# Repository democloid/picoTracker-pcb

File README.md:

# PCB for PicoTrackerPortable
All data in order to fabricate the PCB for the portable version of [picoTracker](https://github.com/democloid/picoTracker)

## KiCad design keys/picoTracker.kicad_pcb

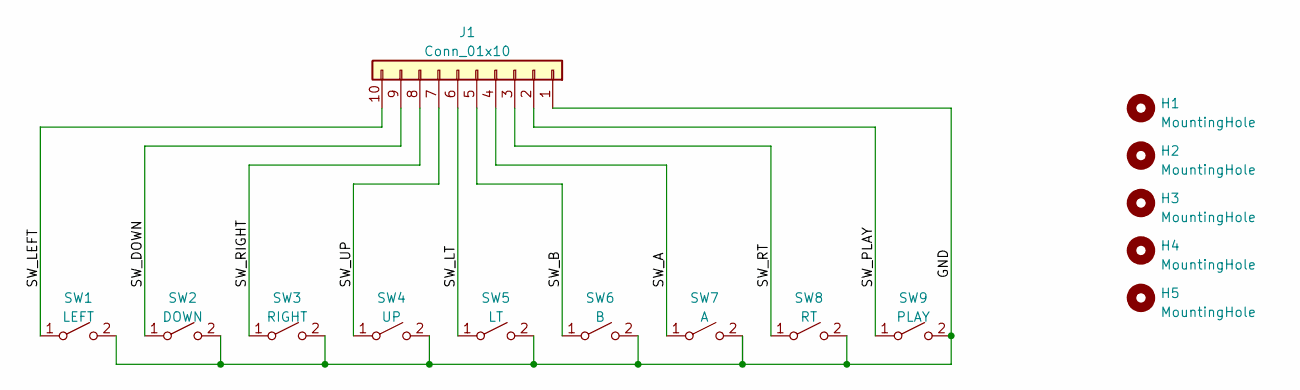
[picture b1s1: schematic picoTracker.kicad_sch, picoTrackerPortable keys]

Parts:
H1, H2, H3, H4, H5: MountingHole; MountingHole_2.2mm_M2
J1: Conn_01x10; PinHeader_1x10_P2.54mm_Vertical
SW1: LEFT; Cherry-MX-Low-Profile
SW2: DOWN; Cherry-MX-Low-Profile
SW3: RIGHT; Cherry-MX-Low-Profile
SW4: UP; Cherry-MX-Low-Profile
SW5: LT; Cherry-MX-Low-Profile
SW6: B; Cherry-MX-Low-Profile
SW7: A; Cherry-MX-Low-Profile
SW8: RT; Cherry-MX-Low-Profile
SW9: PLAY; Cherry-MX-Low-Profile

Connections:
/GND: J1.1, SW1.2 (B), SW2.2 (B), SW3.2 (B), SW4.2 (B), SW5.2 (B), SW6.2 (B), SW7.2 (B), SW8.2 (B), SW9.2 (B)
/SW_A: J1.4, SW7.1 (A)
/SW_B: J1.5, SW6.1 (A)
/SW_DOWN: J1.9, SW2.1 (A)
/SW_LEFT: J1.10, SW1.1 (A)
/SW_LT: J1.6, SW5.1 (A)
/SW_PLAY: J1.2, SW9.1 (A)
/SW_RIGHT: J1.8, SW3.1 (A)
/SW_RT: J1.3, SW8.1 (A)
/SW_UP: J1.7, SW4.1 (A)

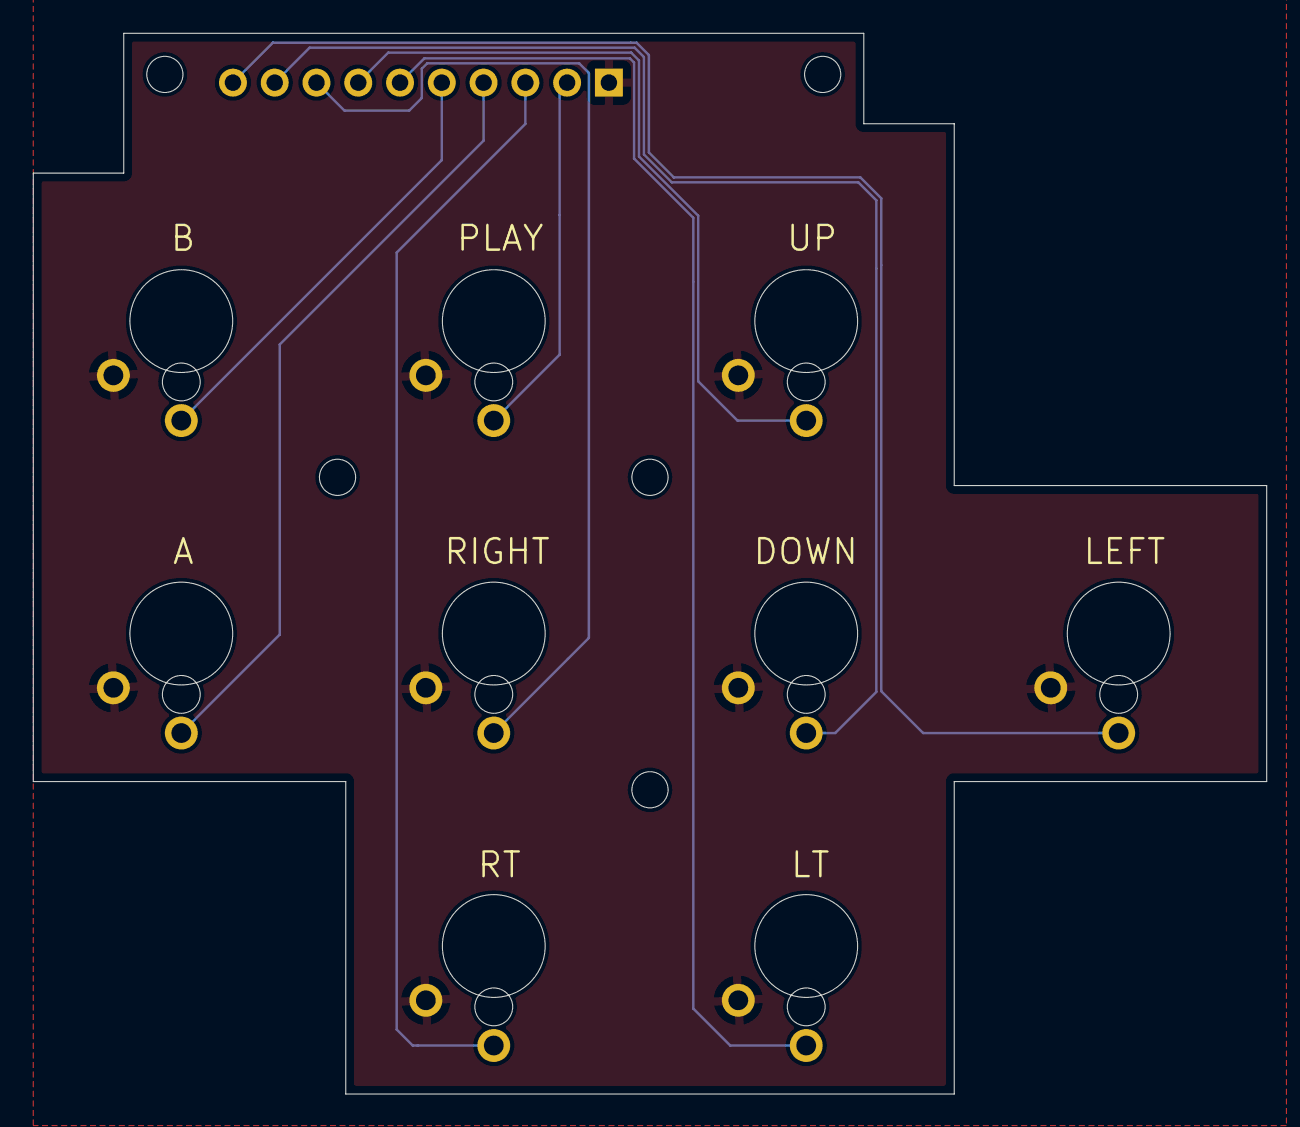
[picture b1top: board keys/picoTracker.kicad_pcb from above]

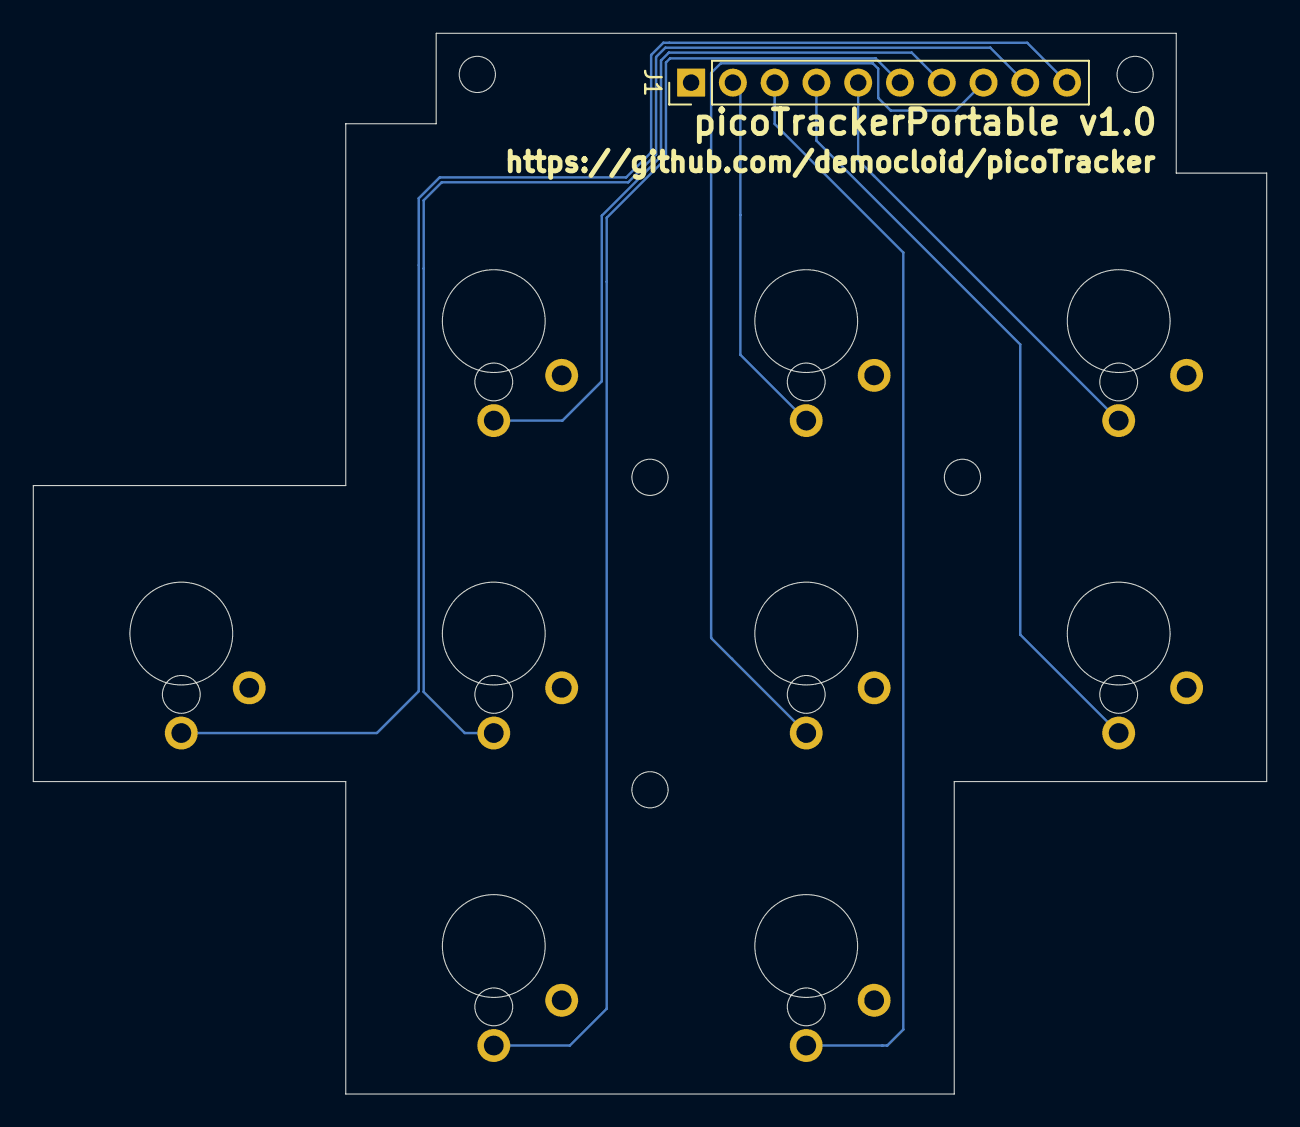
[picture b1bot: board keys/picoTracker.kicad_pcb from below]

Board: 2 copper layers, 75.0 x 64.5 mm, 15 parts (10 on the bottom side), 10 nets.

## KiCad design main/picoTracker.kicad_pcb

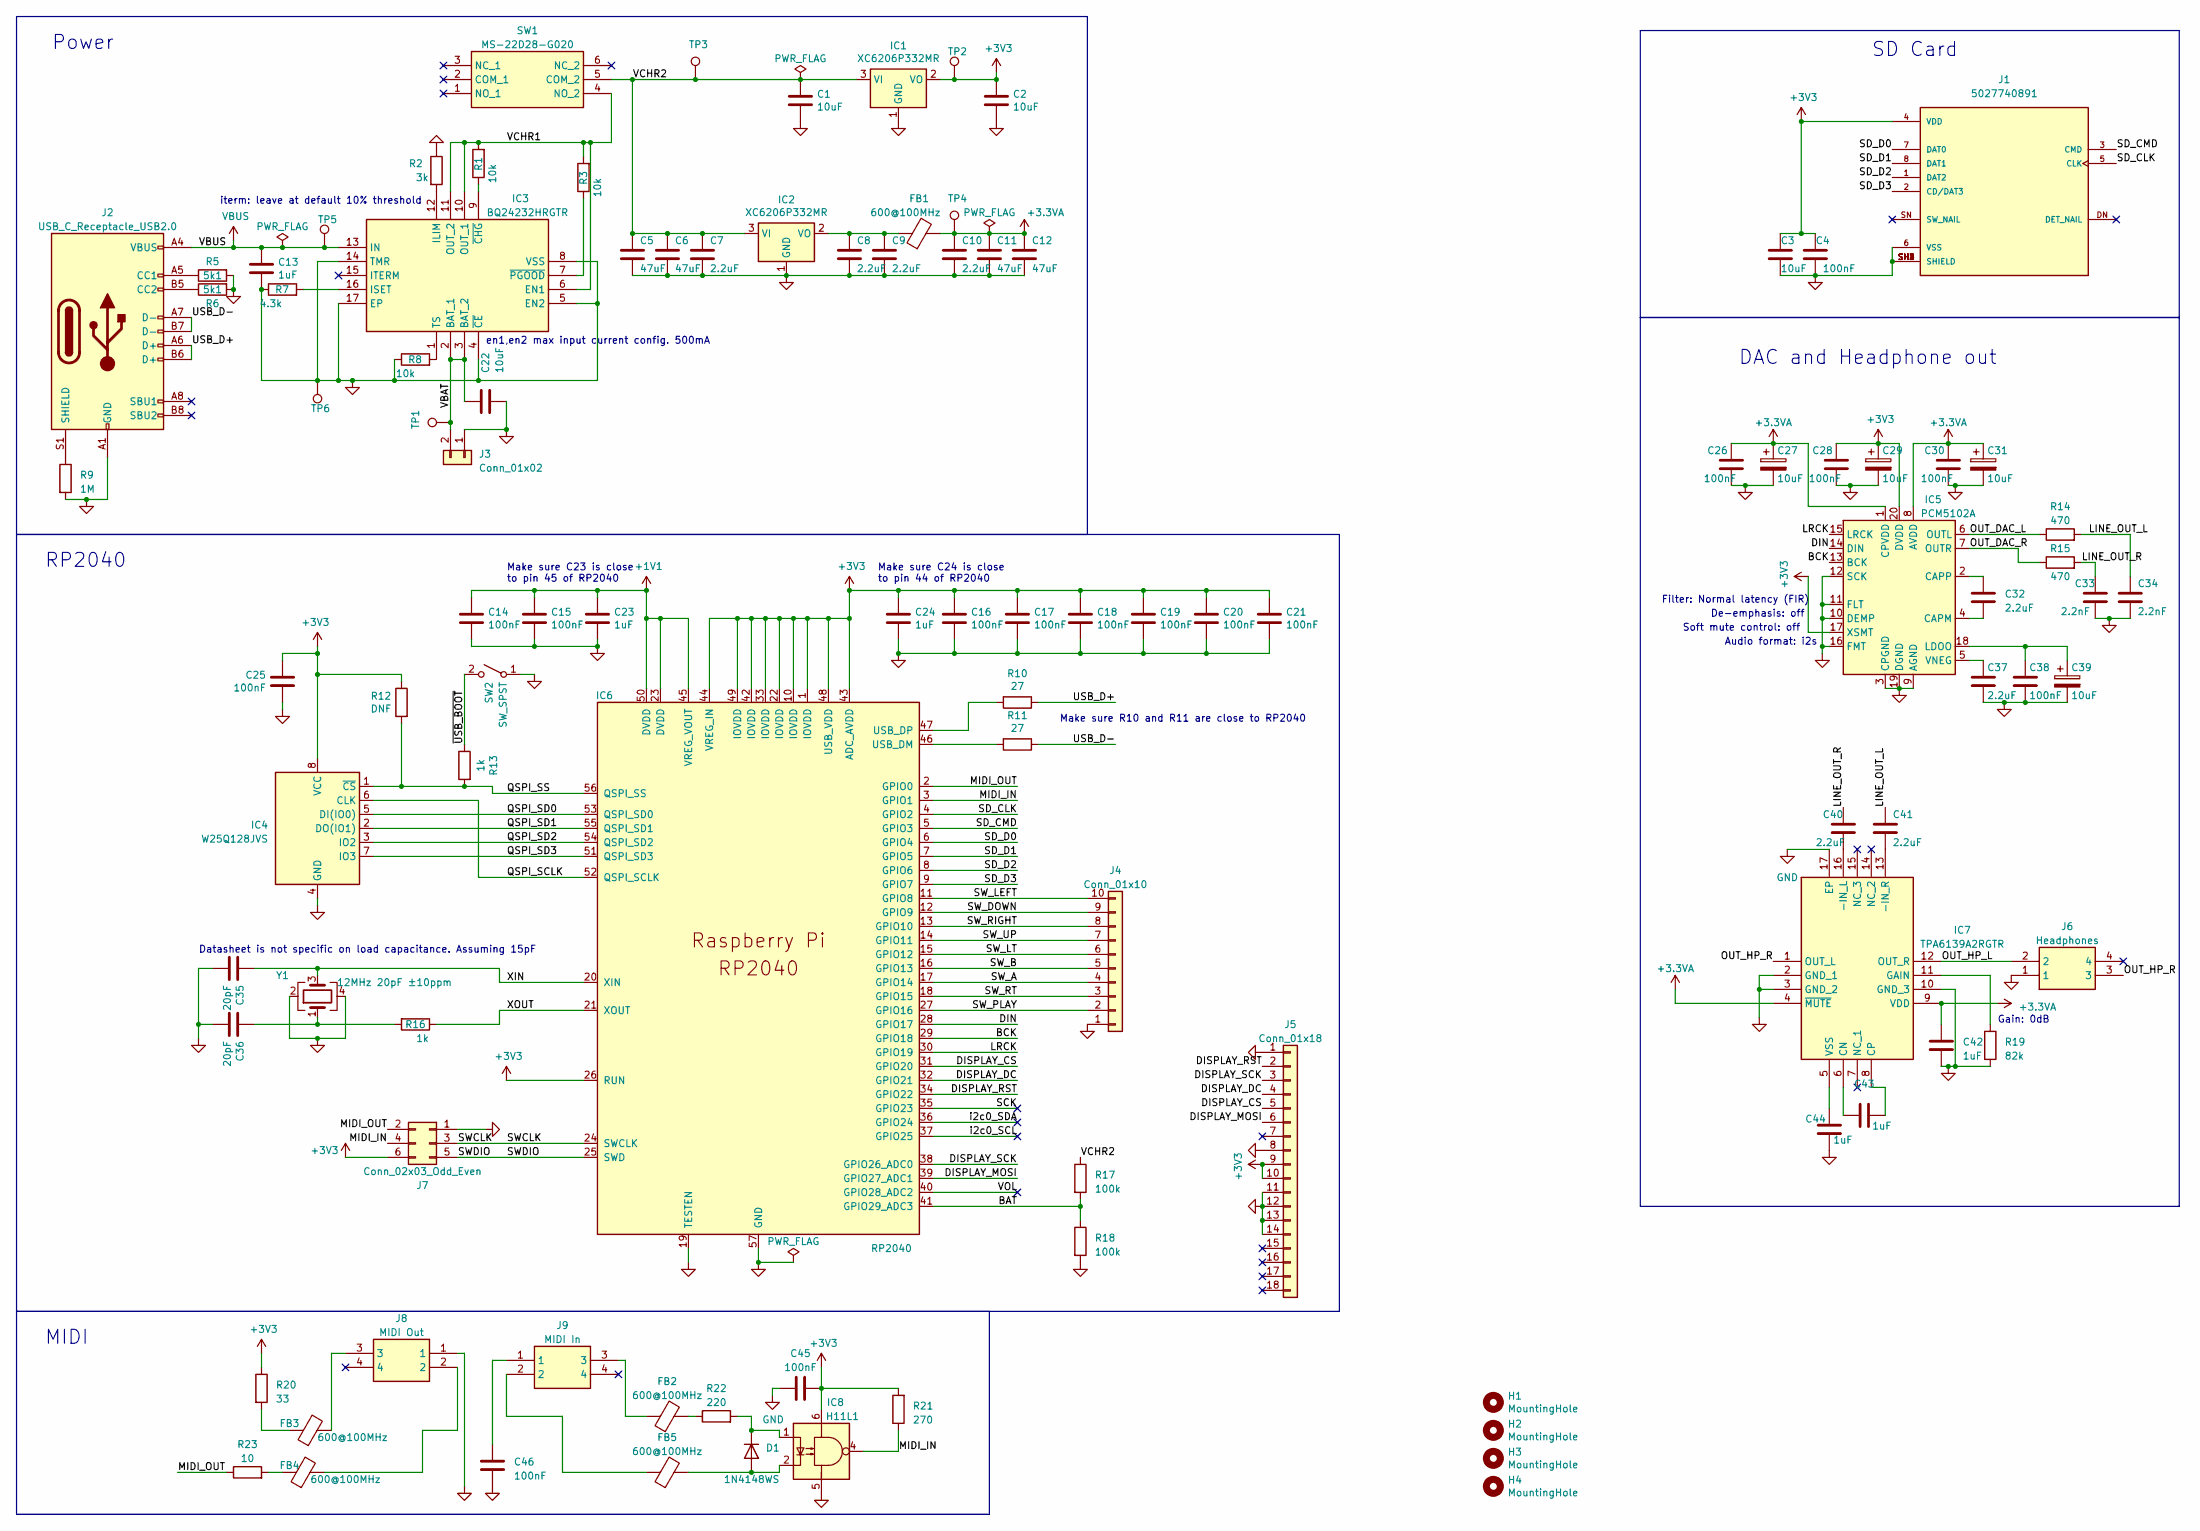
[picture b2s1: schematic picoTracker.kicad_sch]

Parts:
C1, C2, C3, C22: 10uF; C_0603_1608Metric; LCSC C19702
C4, C14, C15, C16, C17, C18, C19, C20, C21, C25, C26, C28, C30, C38, C45, C46: 100nF; C_0603_1608Metric; LCSC C14663
C5, C6, C11, C12: 47uF; C_0805_2012Metric; LCSC C16780
C7, C8, C9, C10, C32, C37, C40, C41: 2.2uF; C_0603_1608Metric; LCSC C23630
C13, C23, C24, C42, C43, C44: 1uF; C_0603_1608Metric; LCSC C15849
C27, C29, C31, C39: 10uF; CP_EIA-3216-18_Kemet-A; LCSC C7171
C33, C34: 2.2nF; C_0603_1608Metric; LCSC C1604
C35, C36: 20pF; C_0603_1608Metric; LCSC C1648
D1: 1N4148WS; D_SOD-323; LCSC C2128
FB1, FB2, FB3, FB4, FB5: 600@100MHz; R_0805_2012Metric; LCSC C1017
H1, H2, H3, H4: MountingHole; MountingHole_2.2mm_M2
IC1, IC2: XC6206P332MR; SOT-23; LCSC C5446
IC3: BQ24232HRGTR; QFN50P300X300X100-17N-D; Mouser Part Number 595-BQ24232HRGTR
IC4: W25Q128JVS; SOIC-8_5.23x5.23mm_P1.27mm; LCSC C97521
IC5: PCM5102A; TSSOP-20_4.4x6.5mm_P0.65mm; LCSC C107671
IC6: RP2040; QFN-56-1EP_7x7mm_P0.4mm_EP3.2x3.2mm; LCSC C2040
IC7: TPA6139A2RGTR; QFN50P300X300X100-17N-D; Mouser Part Number 595-TPA6139A2RGTR
IC8: H11L1; SMDIP-6_W9.53mm; LCSC C78589
J1: 5027740891; MOLEX_5027740891; PARTREV D; LCSC C330255
J2: USB_C_Receptacle_USB2.0; USB_C_Receptacle_G-Switch_GT-USB-7010ASV; LCSC C2988369
J3: Conn_01x02; PinHeader_1x02_P2.54mm_Vertical
J4: Conn_01x10; PinHeader_1x10_P2.54mm_Vertical
J5: Conn_01x18; QD-TFT2803
J6: Headphones; PJ327C4A; Manufacturer_Part_Number PJ-327C-4A; LCSC C145813
J7: Conn_02x03_Odd_Even; PinHeader_2x03_P2.54mm_Vertical
J8: MIDI Out; PJ327C4A; Manufacturer_Part_Number PJ-327C-4A; LCSC C145813
J9: MIDI In; PJ327C4A; Manufacturer_Part_Number PJ-327C-4A; LCSC C145813
R1, R3, R8: 10k; R_0603_1608Metric; LCSC C25804
R2: 3k; R_0603_1608Metric; LCSC C4211
R5, R6: 5k1; R_0603_1608Metric; LCSC C23186
R7: 4.3k; R_0603_1608Metric; LCSC C23159
R9: 1M; R_0603_1608Metric; LCSC C22935
R10, R11: 27; R_0603_1608Metric; LCSC C25190
R12: DNF; R_0603_1608Metric
R13, R16: 1k; R_0603_1608Metric; LCSC C21190
R14, R15: 470; R_0603_1608Metric; LCSC C23179
R17, R18: 100k; R_0603_1608Metric; LCSC C25803
R19: 82k; R_0805_2012Metric; LCSC C17840
R20: 33; R_0603_1608Metric; LCSC C23140
R21: 270; R_0603_1608Metric; LCSC C22966
R22: 220; R_0402_1005Metric; LCSC C25905
R23: 10; R_0603_1608Metric; LCSC C22859
SW1: MS-22D28-G020; MS22D28G020; Manufacturer_Part_Number MS-22D28-G020; LCSC C963205
SW2: SW_SPST; SW_Push_1P1T_XKB_TS-1187A; LCSC C318884
TP1: VBAT; TestPoint_Pad_D1.0mm
TP2: TestPoint; TestPoint_Pad_D1.0mm
TP3: VCHR; TestPoint_Pad_D1.0mm
TP4: 3.3VA; TestPoint_Pad_D1.0mm
TP5: VBUS; TestPoint_Pad_D1.0mm
TP6: GND; TestPoint_Pad_D1.0mm
Y1: 12MHz 20pF ±10ppm; Crystal_SMD_3225-4Pin_3.2x2.5mm; LCSC C9002

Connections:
+1V1: C14.1, C15.1, C23.1, IC6.23 (DVDD), IC6.45 (VREG_VOUT), IC6.50 (DVDD)
+3.3VA: C10.1, C11.1, C12.1, C26.1, C27.1, C30.1, C31.1, C42.1, FB1.2, IC5.1 (CPVDD), IC5.8 (AVDD), IC7.4 (~MUTE), IC7.9 (VDD), TP4.1
+3V3: C2.1, C3.1, C4.1, C16.1, C17.1, C18.1, C19.1, C20.1, C21.1, C24.1, C25.1, C28.1, C29.1, C45.2, IC1.2 (VO), IC4.8 (VCC), IC5.17 (XSMT), IC5.20 (DVDD), IC6.1 (IOVDD), IC6.10 (IOVDD), IC6.22 (IOVDD), IC6.26 (RUN), IC6.33 (IOVDD), IC6.42 (IOVDD), IC6.43 (ADC_AVDD), IC6.44 (VREG_IN), IC6.48 (USB_VDD), IC6.49 (IOVDD), IC8.6, J1.4 (VDD), J5.9, J5.10, J7.6, R12.1, R20.1, R21.2, TP2.1
/BAT: IC6.41 (GPIO29_ADC3), R17.2, R18.1
/BCK: IC5.13 (BCK), IC6.29 (GPIO18)
/DIN: IC5.14 (DIN), IC6.28 (GPIO17)
/DISPLAY_CS: IC6.31 (GPIO20), J5.5
/DISPLAY_DC: IC6.32 (GPIO21), J5.4
/DISPLAY_MOSI: IC6.39 (GPIO27_ADC1), J5.6
/DISPLAY_RST: IC6.34 (GPIO22), J5.2
/DISPLAY_SCK: IC6.38 (GPIO26_ADC0), J5.3
/LINE_OUT_L: C34.1, C41.1, R14.2
/LINE_OUT_R: C33.1, C40.1, R15.2
/LRCK: IC5.15 (LRCK), IC6.30 (GPIO19)
/MIDI_IN: IC6.3 (GPIO1), IC8.4, J7.4, R21.1
/MIDI_OUT: IC6.2 (GPIO0), J7.2, R23.1
/OUT_DAC_L: IC5.6 (OUTL), R14.1
/OUT_DAC_R: IC5.7 (OUTR), R15.1
/OUT_HP_L: IC7.12 (OUT_R), J6.2
/OUT_HP_R: IC7.1 (OUT_L), J6.3
/QSPI_SCLK: IC4.6 (CLK), IC6.52 (QSPI_SCLK)
/QSPI_SD0: IC4.5 (DI(IO0)), IC6.53 (QSPI_SD0)
/QSPI_SD1: IC4.2 (DO(IO1)), IC6.55 (QSPI_SD1)
/QSPI_SD2: IC4.3 (IO2), IC6.54 (QSPI_SD2)
/QSPI_SD3: IC4.7 (IO3), IC6.51 (QSPI_SD3)
/QSPI_SS: IC4.1 (~CS), IC6.56 (QSPI_SS), R12.2, R13.2
/SCK: IC6.35 (GPIO23)
/SD_CLK: IC6.4 (GPIO2), J1.5 (CLK)
/SD_CMD: IC6.5 (GPIO3), J1.3 (CMD)
/SD_D0: IC6.6 (GPIO4), J1.7 (DAT0)
/SD_D1: IC6.7 (GPIO5), J1.8 (DAT1)
/SD_D2: IC6.8 (GPIO6), J1.1 (DAT2)
/SD_D3: IC6.9 (GPIO7), J1.2 (CD/DAT3)
/SWCLK: IC6.24 (SWCLK), J7.3
/SWDIO: IC6.25 (SWD), J7.5
/SW_A: IC6.17 (GPIO14), J4.4
/SW_B: IC6.16 (GPIO13), J4.5
/SW_DOWN: IC6.12 (GPIO9), J4.9
/SW_LEFT: IC6.11 (GPIO8), J4.10
/SW_LT: IC6.15 (GPIO12), J4.6
/SW_PLAY: IC6.27 (GPIO16), J4.2
/SW_RIGHT: IC6.13 (GPIO10), J4.8
/SW_RT: IC6.18 (GPIO15), J4.3
/SW_UP: IC6.14 (GPIO11), J4.7
/USB_D+: J2.A6 (D+), J2.B6 (D+), R10.1
/USB_D-: J2.A7 (D-), J2.B7 (D-), R11.1
/VBAT: C22.1, IC3.2 (BAT_1), IC3.3 (BAT_2), J3.2, TP1.1
/VCHR1: IC3.6 (EN1), IC3.10 (OUT_1), IC3.11 (OUT_2), R1.2, R3.2, SW1.4 (NO_2)
/VCHR2: C1.1, C5.1, C6.1, C7.1, IC1.3 (VI), IC2.3 (VI), R17.1, SW1.5 (COM_2), TP3.1
/VOL: IC6.40 (GPIO28_ADC2)
/XIN: C35.1, IC6.20 (XIN), Y1.3
/XOUT: IC6.21 (XOUT), R16.1
/i2c0_SCL: IC6.37 (GPIO25)
/i2c0_SDA: IC6.36 (GPIO24)
/~USB_BOOT: R13.1, SW2.2 (B)
GND: C1.2, C2.2, C3.2, C4.2, C5.2, C6.2, C7.2, C8.2, C9.2, C10.2, C11.2, C12.2, C13.2, C14.2, C15.2, C16.2, C17.2, C18.2, C19.2, C20.2, C21.2, C22.2, C23.2, C24.2, C25.2, C26.2, C27.2, C28.2, C29.2, C30.2, C31.2, C33.2, C34.2, C35.2, C36.2, C37.2, C38.2, C39.2, C42.2, C44.2, C45.1, C46.2, IC1.1 (GND), IC2.1 (GND), IC3.4 (~CE), IC3.5 (EN2), IC3.8 (VSS), IC3.14 (TMR), IC3.17 (EP), IC4.4 (GND), IC5.3 (CPGND), IC5.9 (AGND), IC5.10 (DEMP), IC5.11 (FLT), IC5.12 (SCK), IC5.16 (FMT), IC5.19 (DGND), IC6.19 (TESTEN), IC6.57 (GND), IC7.2 (GND_1), IC7.3 (GND_2), IC7.10 (GND_3), IC7.17 (EP), IC8.5, J1.6 (VSS), J1.SH1 (SHIELD), J1.SH2 (SHIELD), J1.SH3 (SHIELD), J1.SH4 (SHIELD), J2.A1 (GND), J2.A12 (GND), J2.B1 (GND), J2.B12 (GND), J3.1, J4.1, J5.1, J5.8, J5.11, J5.12, J5.13, J5.14, J6.1, J7.1, J8.1, R2.1, R5.2, R6.2, R7.1, R8.1, R9.2, R18.2, R19.2, SW2.1 (A), TP6.1, Y1.2, Y1.4
unnamed: C36.1, R16.2, Y1.1
unnamed: C46.1, J9.1
unnamed: D1.2 (A), FB5.2, IC8.2
unnamed: D1.1 (K), IC8.1, R22.2
unnamed: FB2.1, J9.3
unnamed: FB2.2, R22.1
unnamed: FB3.1, R20.2
unnamed: FB3.2, J8.3
unnamed: FB4.1, R23.2
unnamed: FB4.2, J8.2
unnamed: FB5.1, J9.2
unnamed: C8.1, C9.1, FB1.1, IC2.2 (VO)
unnamed: IC3.12 (ILIM), R2.2
unnamed: IC3.16 (ISET), R7.2
unnamed: IC3.1 (TS), R8.2
unnamed: IC3.9 (~CHG), R1.1
unnamed: IC3.7 (~PGOOD), R3.1
unnamed: C32.2, IC5.4 (CAPM)
unnamed: C32.1, IC5.2 (CAPP)
unnamed: C38.1, C39.1, IC5.18 (LDOO)
unnamed: C37.1, IC5.5 (VNEG)
unnamed: IC6.46 (USB_DM), R11.2
unnamed: IC6.47 (USB_DP), R10.2
unnamed: C40.2, IC7.16 (-IN_L)
unnamed: C41.2, IC7.13 (-IN_R)
unnamed: C43.1, IC7.6 (CN)
unnamed: C43.2, IC7.8 (CP)
unnamed: IC7.11 (GAIN), R19.1
unnamed: C44.1, IC7.5 (VSS)
unnamed: J2.A5 (CC1), R5.1
unnamed: J2.B5 (CC2), R6.1
unnamed: J2.S1 (SHIELD), R9.1
VBUS: C13.1, IC3.13 (IN), J2.A4 (VBUS), J2.A9 (VBUS), J2.B4 (VBUS), J2.B9 (VBUS), TP5.1

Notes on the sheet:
DAC and Headphone out
iterm: leave at default 10% threshold
SD Card
en1,en2 max input current config. 500mA
Power
RP2040
Filter: Normal latency (FIR)
Datasheet is not specific on load capacitance. Assuming 15pF
Make sure C23 is close to pin 45 of RP2040
Soft mute control: off
Make sure R10 and R11 are close to RP2040
Gain: 0dB
De-emphasis: off
MIDI
Audio format: i2s
Make sure C24 is close to pin 44 of RP2040

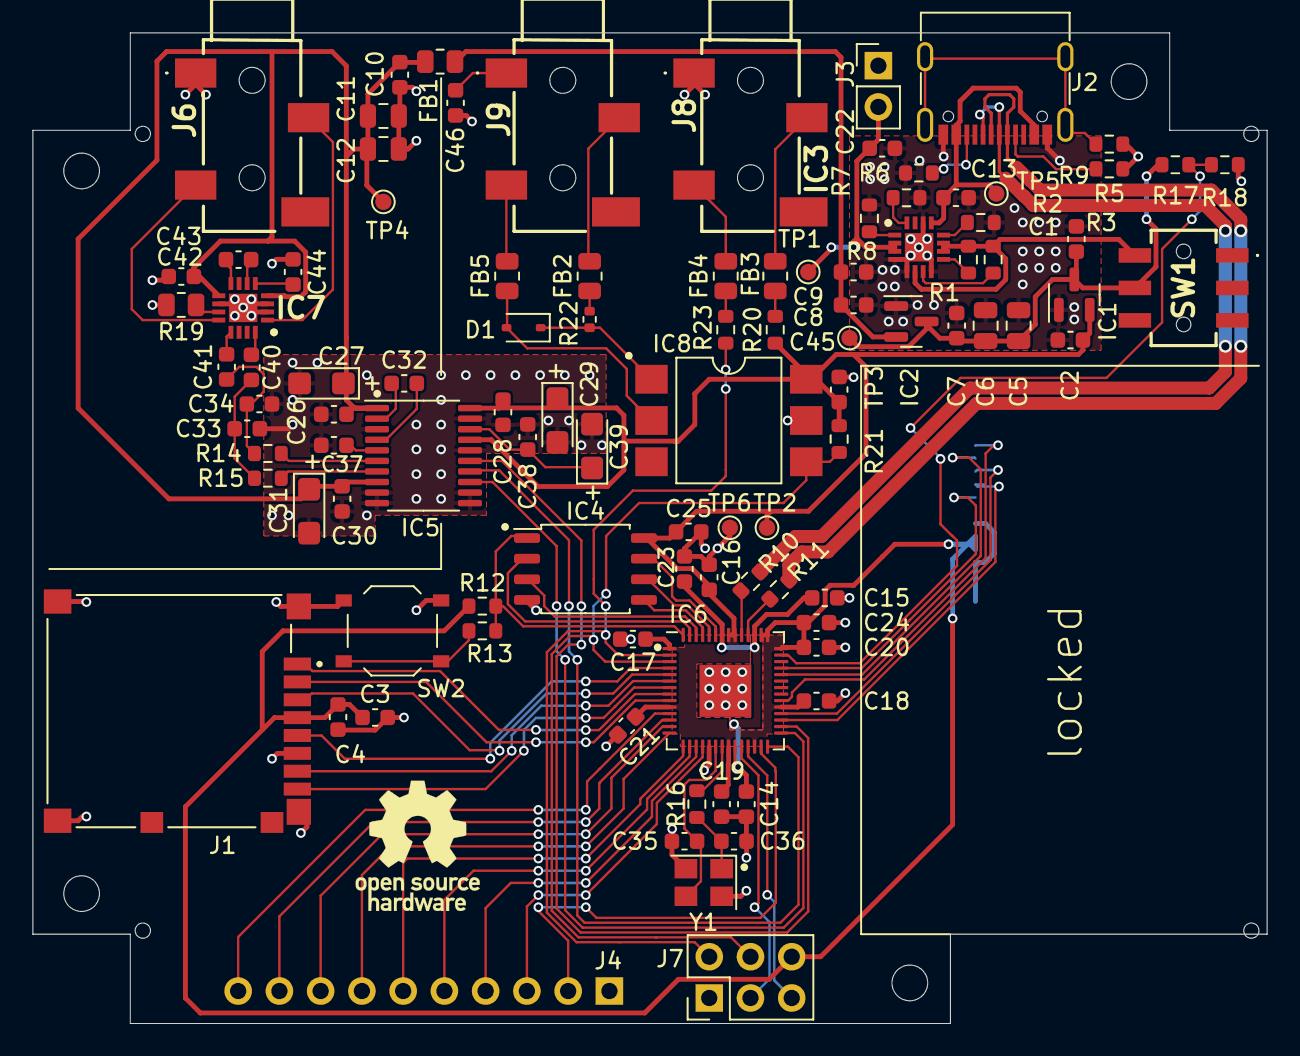
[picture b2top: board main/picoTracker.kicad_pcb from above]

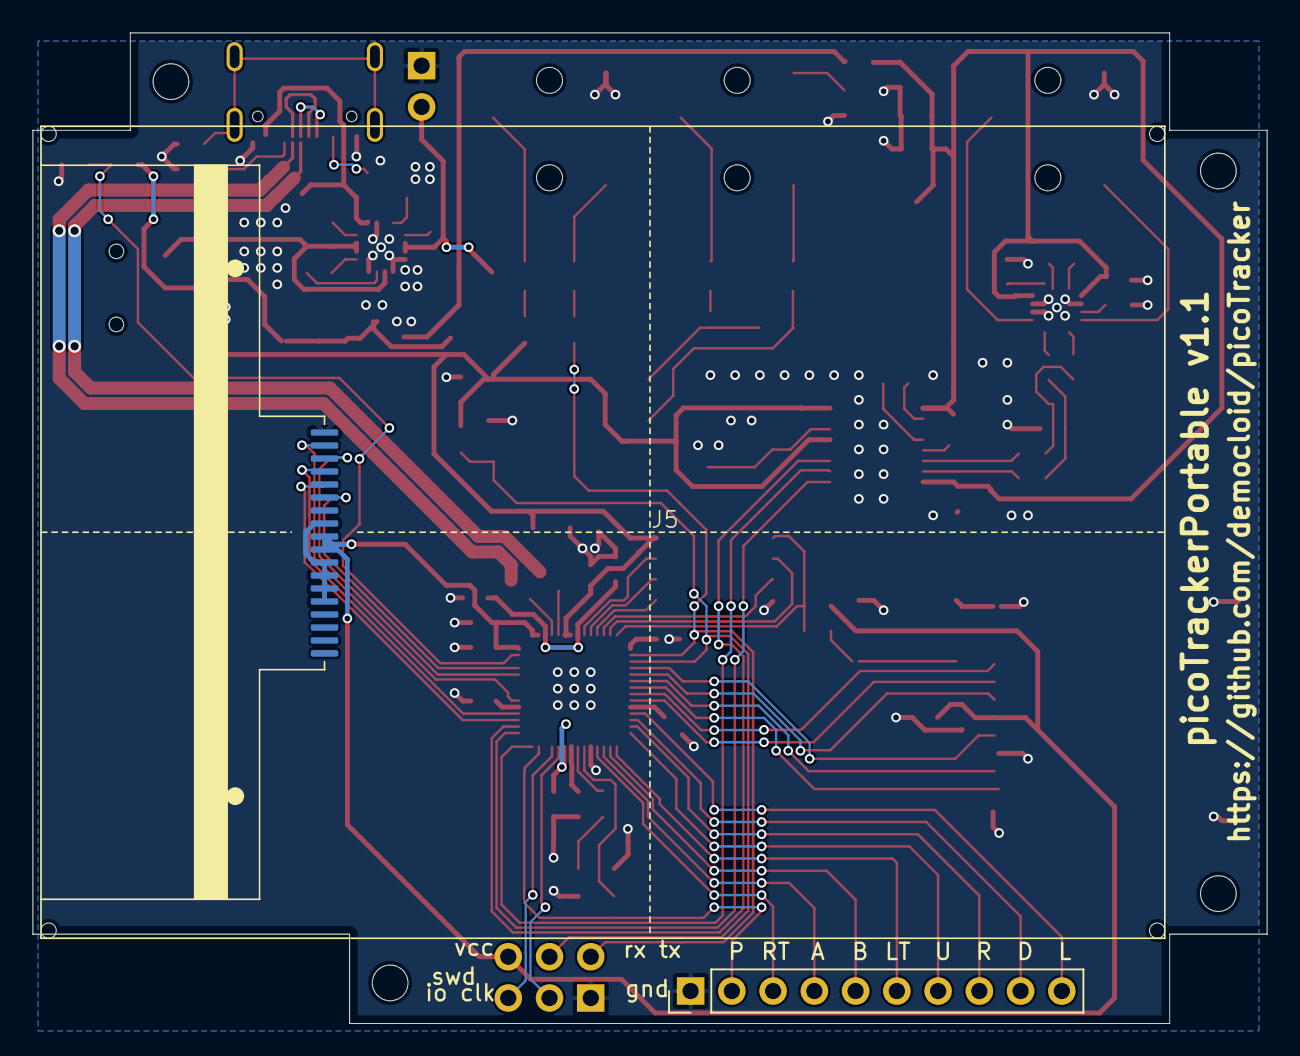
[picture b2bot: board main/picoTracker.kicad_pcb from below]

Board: 2 copper layers, 76.0 x 61.0 mm, 104 parts (6 on the bottom side), 85 nets.

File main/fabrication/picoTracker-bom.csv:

Comment,Designator,Footprint,LCSC
"10uF","C1,C2,C3,C22","Capacitor_SMD:C_0603_1608Metric","C19702"
"1uF","C13,C23,C24,C42,C43,C44","Capacitor_SMD:C_0603_1608Metric","C15849"
"10uF","C27,C29,C31,C39","Capacitor_Tantalum_SMD:CP_EIA-3216-18_Kemet-A","C7171"
"2.2nF","C33,C34","Capacitor_SMD:C_0603_1608Metric","C1604"
"20pF","C35,C36","Capacitor_SMD:C_0603_1608Metric","C1648"
"100nF","C4,C14,C15,C16,C17,C18,C19,C20,C21,C25,C26,C28,C30,C38,C45,C46","Capacitor_SMD:C_0603_1608Metric","C14663"
"47uF","C5,C6,C11,C12","Capacitor_SMD:C_0805_2012Metric","C16780"
"2.2uF","C7,C8,C9,C10,C32,C37,C40,C41","Capacitor_SMD:C_0603_1608Metric","C23630"
"1N4148WS","D1","Diode_SMD:D_SOD-323","C2128"
"600@100MHz","FB1,FB2,FB3,FB4,FB5","Resistor_SMD:R_0805_2012Metric","C1017"
"XC6206P332MR","IC1,IC2","Package_TO_SOT_SMD:SOT-23","C5446"
"BQ24232HRGTR","IC3","project:QFN50P300X300X100-17N-D","C575586"
"W25Q128JVS","IC4","project:SOIC-8_5.23x5.23mm_P1.27mm","C97521"
"PCM5102A","IC5","Package_SO:TSSOP-20_4.4x6.5mm_P0.65mm","C107671"
"RP2040","IC6","Package_DFN_QFN:QFN-56-1EP_7x7mm_P0.4mm_EP3.2x3.2mm","C2040"
"TPA6139A2RGTR","IC7","project:QFN50P300X300X100-17N-D","C2868391"
"H11L1","IC8","Package_DIP:SMDIP-6_W9.53mm","C78589"
"5027740891","J1","project:MOLEX_5027740891","C330255"
"USB_C_Receptacle_USB2.0","J2","project:USB_C_Receptacle_G-Switch_GT-USB-7010ASV","C2988369"
"Headphones","J6","project:PJ327C4A","C145813"
"MIDI Out","J8","project:PJ327C4A","C145813"
"MIDI In","J9","project:PJ327C4A","C145813"
"10k","R1,R3,R8","Resistor_SMD:R_0603_1608Metric","C25804"
"27","R10,R11","Resistor_SMD:R_0603_1608Metric","C25190"
"1k","R13,R16","Resistor_SMD:R_0603_1608Metric","C21190"
"470","R14,R15","Resistor_SMD:R_0603_1608Metric","C23179"
"100k","R17,R18","Resistor_SMD:R_0603_1608Metric","C25803"
"82k","R19","Resistor_SMD:R_0805_2012Metric","C17840"
"3k","R2","Resistor_SMD:R_0603_1608Metric","C4211"
"33","R20","Resistor_SMD:R_0603_1608Metric","C23140"
"270","R21","Resistor_SMD:R_0603_1608Metric","C22966"
"220","R22","Resistor_SMD:R_0402_1005Metric","C25905"
"10","R23","Resistor_SMD:R_0603_1608Metric","C22859"
"5k1","R5,R6","Resistor_SMD:R_0603_1608Metric","C23186"
"4.3k","R7","Resistor_SMD:R_0603_1608Metric","C23159"
"1M","R9","Resistor_SMD:R_0603_1608Metric","C22935"
"MS-22D28-G020","SW1","project:MS22D28G020","C963205"
"SW_SPST","SW2","project:SW_Push_1P1T_XKB_TS-1187A","C318884"
"12MHz 20pF ±10ppm","Y1","Crystal:Crystal_SMD_3225-4Pin_3.2x2.5mm","C9002"

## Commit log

2023-06-05 Create LICENSE
